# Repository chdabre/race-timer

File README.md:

# ESP32 7-Segment Race Timer

[![CC BY-SA 4.0][cc-by-sa-shield]][cc-by-sa]

## Overview

A race timing system built with an ESP32-S3 microcontroller and LED display that measures elapsed time between start and finish sensors.

The connection box can provide power to multiple timer modules, and provides a reset button to reset all modules at once.

The system is designed to be easy to use and assemble. The timer modules are designed to be mounted to a table, and all wiring is run underneath the table.

The timer modules are connected to the connection box with a removable connector, so each module can be transported individually.

If more than 2 modules are needed, the connection box can be easily extended with additional connectors.

## Operation

Two light barriers are connected to each timer module, each consisting of a transmitter and receiver.

The START barrier is mounted at the beginning of the race track.
The STOP barrier is mounted at the end of the race track.

When the START barrier is interrupted, the current time measurement is reset and a new timing begins.

When the STOP barrier is interrupted while timing is active, the timing stops and the final time is shown on the display.

If a timing measurement exceeds 100 seconds, the time can no longer be fully displayed. The seconds display resets to 00: and timing continues.

When the RESET button is pressed at any time, the current timing is stopped and the display immediately resets to 00:00.

## Firmware development and flashing

The firmware is developed using the Arduino Platform on PlatformIO. The project is configured for the Adafruit ESP32-S3 Feather board.

### Dependencies

The following libraries are required and will be automatically installed by PlatformIO:

- Wire
- Adafruit LED Backpack Library

### Building and Flashing

1. Install VS Code and the PlatformIO extension
2. Clone this repository
3. Open the project folder in VS Code
4. Connect the Feather Board via USB
5. Click the PlatformIO "Upload" button or press Ctrl+Alt+U

The serial monitor can be opened at 115200 baud to view debug messages.

## Schematics

See also the KiCad project in the `hardware` folder.

**FeatherWing Schematic**

**Connection Box Schematic**

## Bill of Materials

**Per Timer Module**

- 1x 3d printed enclosure (See hardware folder)
- 4x M3 5mm threaded inserts
- 4x M4x6mm threaded inserts
- 4x M3x8mm hex screws
- 4x M4 mounting bolts
- 1x Adafruit ESP32-S3 Feather board (No PSRAM)
- 2x DFRobot Infrared Light Barrier Kit ([SEN0347](https://www.dfrobot.com/product-2057.html))
- 1x Race Timer FeatherWing (See hardware folder)
    - 1x Race Timer FeatherWing PCB 
    - 2x 16-Pin 2.54mm pin headers
    - 1x 5-Pin 2.54mm pin header
    - 2x JST-XH 2.50mm B2B (2-Pin)
    - 2x JST-XH 2.50mm B3B (3-Pin)
    - 1x JST-XH 2.50mm B4B (4-Pin)
    - 2x 10K 1/4W THT Resistor
- 2x JST-XH 2.50mm B2B (2-Pin) Female Connector
- 2x JST-XH 2.50mm B3B (3-Pin) Female Connector
- 1x JST-XH 2.50mm B4B (4-Pin) Female Connector
- 1x GX16 7-Pin Female Connector
- 4-core 20AWG cable to the connection box

**Connection Box**

- 1x 3d printed enclosure (See hardware folder)
- 4x M3 5mm threaded inserts
- 4x M3x8mm hex screws
- 1x Mini360 DC-DC Converter (or similar) 9-24V to 5V
- 2x GX16 7-Pin Male Connector
- 1x DC00990 Panel mount 5.5x2.1mm barrel jack connector
- 1x Generic 8mm panel mount push button switch
- 1x 12V 1A Power Supply 5.5x2.1mm barrel jack, center positive
- Wires for internal connections

## License

This work is licensed under a
[Creative Commons Attribution-ShareAlike 4.0 International License][cc-by-sa].

[![CC BY-SA 4.0][cc-by-sa-image]][cc-by-sa]

[cc-by-sa]: http://creativecommons.org/licenses/by-sa/4.0/
[cc-by-sa-image]: https://licensebuttons.net/l/by-sa/4.0/88x31.png
[cc-by-sa-shield]: https://img.shields.io/badge/License-CC%20BY--SA%204.0-lightgrey.svg

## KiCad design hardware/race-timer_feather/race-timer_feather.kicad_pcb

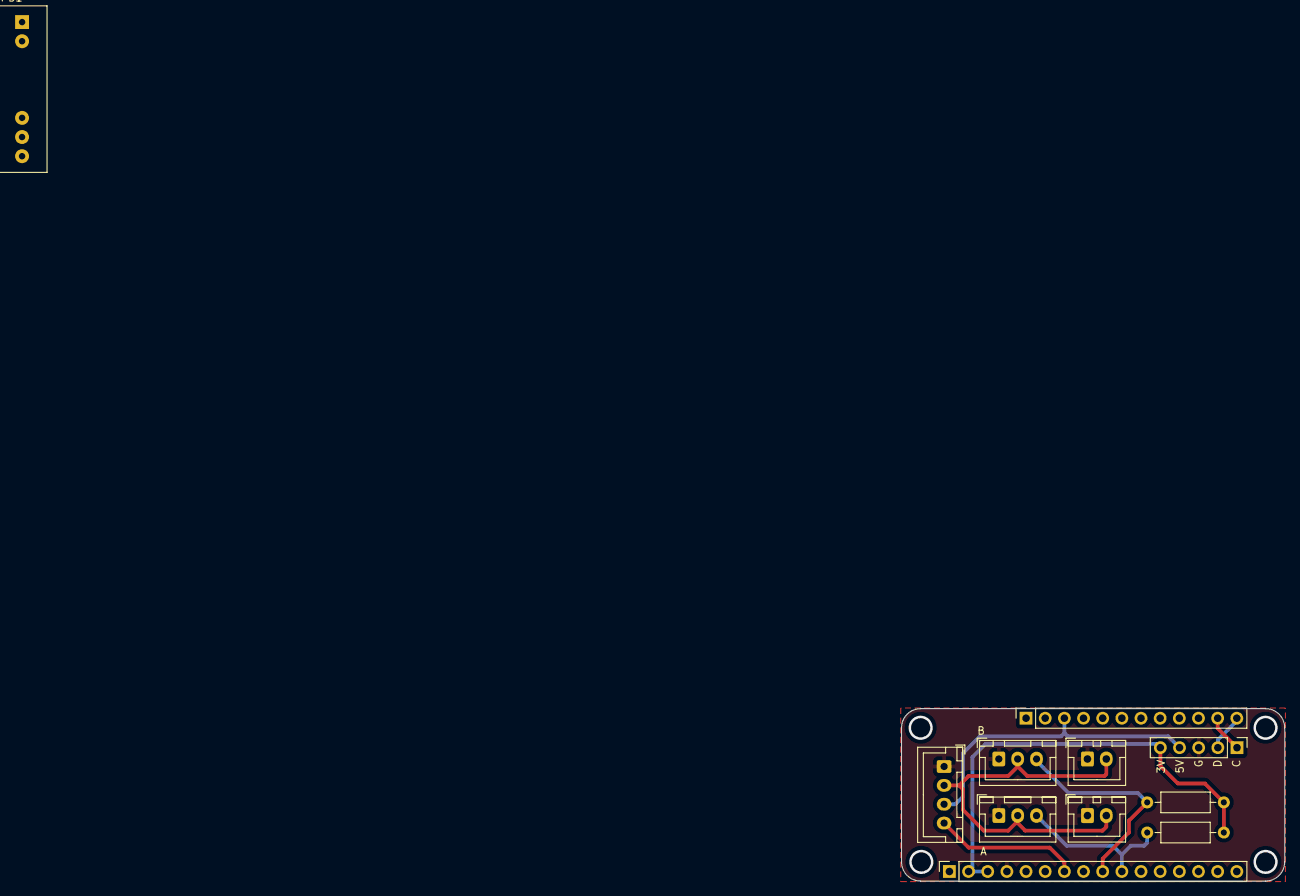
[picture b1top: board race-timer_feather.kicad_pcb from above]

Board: 2 copper layers, 50.8 x 22.9 mm, 11 parts (0 on the bottom side), 10 nets.

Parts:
J1: PinSocket_1x16_P2.54mm_Vertical
J2: PinSocket_1x12_P2.54mm_Vertical
J3: SENSOR1_RX; JST_XH_B3B-XH-A_1x03_P2.50mm_Vertical
J4: SENSOR2_RX; JST_XH_B3B-XH-A_1x03_P2.50mm_Vertical
J5: SENSOR1_TX; JST_XH_B2B-XH-A_1x02_P2.50mm_Vertical
J6: SENSOR2_TX; JST_XH_B2B-XH-A_1x02_P2.50mm_Vertical
J7: PWR; JST_XH_B4B-XH-A_1x04_P2.50mm_Vertical
J8: DISP; PinHeader_1x05_P2.54mm_Vertical
PS1: 5V DC-DC Converter; Converter_DCDC_XP_POWER-ITXxxxxSA_THT
R1, R2: 10K; R_Axial_DIN0207_L6.3mm_D2.5mm_P10.16mm_Horizontal

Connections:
+3.3V: J1.2, J1.3, J8.5, R1.2, R2.2
+5V: J2.3, J7.3, J8.4
/+12V: J3.2, J4.2, J5.2, J6.2, J7.2
/GND: J1.4, J3.1, J4.1, J5.1, J6.1, J7.1, J8.3
/SCL: J2.11, J8.1
/SDA: J2.12, J8.2
GND: PS1.1 (-Vin), PS1.7 (-Vout)
RESET: J1.7, J7.4
S1: J1.10, J3.3, R1.1
S2: J1.9, J4.3, R2.1

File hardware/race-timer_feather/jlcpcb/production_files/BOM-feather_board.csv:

Comment,Designator,Footprint,LCSC
PWR,J7,JST_XH_B4B-XH-A_1x04_P2.50mm_Vertical,
SENSOR2_TX,J6,JST_XH_B2B-XH-A_1x02_P2.50mm_Vertical,
SENSOR1_TX,J5,JST_XH_B2B-XH-A_1x02_P2.50mm_Vertical,
SENSOR2_RX,J4,JST_XH_B3B-XH-A_1x03_P2.50mm_Vertical,
SENSOR1_RX,J3,JST_XH_B3B-XH-A_1x03_P2.50mm_Vertical,
10K,R2,R_Axial_DIN0207_L6.3mm_D2.5mm_P10.16mm_Horizontal,
10K,R1,R_Axial_DIN0207_L6.3mm_D2.5mm_P10.16mm_Horizontal,
DISP,J8,PinHeader_1x05_P2.54mm_Vertical,
Conn_01x12_Female,J2,PinSocket_1x12_P2.54mm_Vertical,
Conn_01x16_Female,J1,PinSocket_1x16_P2.54mm_Vertical,
